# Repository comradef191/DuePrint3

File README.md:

# DuePrint3
Duet 3 to Stratasys PDB Interface Board. Used to convert a Stratasys Prodigy series printer (Dimension, uPrint, Fortus 250) to use a modern control board & firmware. This conversion is fully reversable (assuming the printer functions to begin with). Many thanks to AJ Quick and Archeantus (Jeremy) for their past efforts in detailing the electronics of the Dimension/uPrint machines, as well as sharing details on their Duet 2 WiFi conversions.
* https://wiki.cnc.xyz/Stratasys_uPrint_Retrofit
* https://forum.duet3d.com/topic/12647/another-stratasys-uprint-retrofit

[Additional details for this project on the Duet3D forums.](https://forum.duet3d.com/topic/37434/dueprint-with-a-duet-3-6hc-stratasys-dimension-conversion)

At present, the implementation focuses on the Dimension 1200es printers (the implementations linked above focus on the uPrint series, which is quite similar. The electronics are laid out a touch differently, meaning the layout of the new hardware must change, as well where the stepper motor wiring taps in to the existing harness). The Duet 3 Mainboard 6HC, as well as the Sammy-C21 module (natively running RepRapFirmware) interface with 19 inputs, and 9 outputs.
### Inputs
|Input|Description|GCode|Note|
|---|---|---|---|
|6HC IO_7 io7.in|PRINT HEAD TEMP ALARM|`M950 J9 C"!io7.in" ; Print Head Temp Alarm`|Feature not yet implemented|
|6HC IO_2 io2.in|PRINT BED TOUCH PR LIM SW|`M558 P5 H5 F1200:200 T18000 A3 C"!io2.in" ; Z probe`|Used in bed probing|
|6HC IO_6 io6.in|Z-AXIS EOT|`M574 Z2 S1 P"!io6.in"  ; assign Z EOT to x endstop on high side`|Used as part of homing (find max Z)|
|6HC IO_8 io8.in|CHAMBER TEMP ALARM|`M950 J10 C"!io8.in" ; Chamber Temp Alarm`|Feature not yet implemented|
|6HC IO_4 io4.in|Y-AXIS EOT|`M950 J6 C"!io4.in" ; Y-axis EOT`|Used in macro to measure max Y|
|6HC IO_3 io3.in|X-AXIS EOT|`M950 J5 C"!io3.in" ; X-axis EOT`|Used in macro to measure max X|
|6HC IO_0 io0.in|X-AXIS HOME SW|`M574 X1 S1 P"!io0.in" ; X home limit (low side)`|Used in homing|
|6HC IO_1 io1.in|Y-AXIS HOME SW|`M574 Y1 S1 P"!io1.in" ; Y home limit (low side)`|Used in homing|
|6HC IO_5 io5.in|Z-AXIS HOME SW|`M950 J7 C"!io5.in" ; Z-axis Home`|I/O works, Feature not yet implemented|
|SAMMY-C21 PB08|Filament Detection 2|Not Implemented|Feature not yet implemented|
|SAMMY-C21 PA04|Gecko Error|`M950 J0 C"124.pa04" ; Gecko Error In`|Was used to detect an error on Geckodrive G320x. No longer used|
|SAMMY-C21 PA05|HEAD THERMOSTAT STATUS|`M950 J1 C"124.pa05" ;Head Thermostat Status`|Feature not yet implemented|
|SAMMY-C21 PA06|DOOR SWITCH|`M950 J2 C"124.pa06" ; Door`|I/O works, Feature not yet implemented|
|SAMMY-C21 PA07|SUPPORT TOGGLE SW|`M950 J3 C"124.pa07" ; Support Toggle`|Sense Support toolchange|
|SAMMY-C21 PA12|Filament Detection 1|Not Implemented|Feature not yet implemented|
|SAMMY-C21 PA19|MODEL TOGGLE SW|`M950 J4 C"124.pa19" ; Model Toggle`|Sense Model toolchange|
|6HC TEMP_0 VSSA & temp0|CHAMBER THERM|`M308 S0 A"Chamber Test" P"temp0" Y"linear-analog" F0 B-42 C113`||
|6HC TEMP_1 VSSA & temp1|MODEL THERM|`M308 S1 A"Model Test" P"temp1" Y"linear-analog" F0 B12.5 C328`||
|6HC TEMP_2 VSSA & temp2|SUPPORT THERM|`M308 S2 A"Support Test" P"temp2" Y"linear-analog" F0 B12.5 C328`||

### Outputs
|Output|Description|GCode|Note|
|---|---|---|---|
|6HC OUT_8 V_OUTLC8 & out8|EXTRUDER MODEL HEATER ENA|`M950 H1 C"!out8" T1 ; Model, sensor 1`|
|6HC OUT_9 V_OUTLC9 & out9|SUPPORT HEATER ENA|`M950 H2 C"!out9" T2 ; Support, sensor 2`|
|6HC IO_2 io2.out|LED LIGHTS ENA|`M950 P4 C""io2.out"" ; LED Lights - M42 P4 S1 ; lights on`|
|6HC IO_6 io6.out|DOOR SOLENOID ENA|`M950 P3 C""io6.out"" ; Door Solenoid - M42 P3 S0 ; unlocked`|
|6HC OUT_7 V_OUTLC7 & out7|CHAMBER HEATER ENA|`M950 H0 C"!out7" T0 ; Chamber, sensor 0`||
|6HC OUT_6 V_OUTLC6 & out6|PRINT BED TOUCH PR ENA|`M950 P2 C""!out6"" ; Touch Power Enable` - `M42 P2 S0`|Unsure on purpose? Doesn't seem to function at all/as expected|
|6HC IO_0 io0.out|GECKO RESET|`M950 P5 C""io0.out"" ; Gecko Reset` - `M42 P5 S0`|Was used to reset an error on Geckodrive G320x. No longer used|
|6HC OUT_5 V_OUTLC5 & out5|MOTOR ENA|`M950 P1 C""!out5"" ; Extruder Motor` - `M42 P1 S0 ; motor off`|
|6HC OUT_4 V_OUTLC4 & out4|BLOWER ENA|`M950 P0 C""!out4"" ; Head Blower Fan` - `M42 P0 S0 ; enable blower`|

The 6HC directly drives the X, Y, and Z stepper motors (vs. controlling them through the Stratasys PDB). The 6HC, unlike the Duet2 (and Duex boards) does not natively have STEP/DIR pins used to emit step and direction pulses. Instead, a Sammy-C21 ([running RepRapFirmware](https://docs.duet3d.com/Duet3D_hardware/Duet_3_family/Using_the_Sammy-C21_development_board_with_Duet_3)) is used to emit step and direction pulses to a STM32 Nucelo-64, which in turn is running [SimpleDCMotor](https://github.com/simplefoc/Arduino-FOC-dcmotor) to control the extruder's closed loop DC motor. Note that this design was initially setup to use a Geckodrive G320x, however early into commissioning, I burnt up a few series resistors and a 74AC14 on the PDB. The Nucleo-64 with SimpleDCMotor is a much better solution, with a significantly lower cost.

## Materials
[A detailed BOM can be found here](https://github.com/jcwebber93/DuePrint3/blob/main/DuePrint3%20BOM.xlsx), with the approximate cost being ~$500 (60% of this is Duet3D 6HC and Sammy-C21).

## Interface Board Design
[The KidCad project for the DuePrint3 board can be found here](https://github.com/jcwebber93/DuePrint3/tree/main/DuePrint3%20KiCad%20Project)

## Wiring
[A detailed wire list can be found here.](https://github.com/jcwebber93/DuePrint3/blob/main/DuePrint3%20Wire%20List.xlsx) Connectors & crimps for the Duet 3 6HC are supplied with the board, but are JST VH (stepper motors) and Molex KK / Wurth WR-WTB (Wurth connectors/contacts are supplied with Duet Boards). Interface board uses Molex Micro-3.0 series connectors & crimps, whereas the connectors for the PBD ribbon cables are Samtec EHT headers.

> [!WARNING]
> Do not connect connectors `P13`, `P20`, and `P26` (Model heater, support heater, chamber heater) to the 6HC until after the model, support, and chamber thermocouple functionality has been validated

## Sammy-C21 Prep
If using a Sammy-C21 purchased with the preloaded Duet3D bootloader, no special programming is needed. J100 needs to be unbridged, as 5V is supplied to pins 15 and 32 (V33, for 5V logic, and VCC).

## Interface Board Prep
If the Interface Board (w/Sammy-C21) is the only CAN-FD device, aside from the Duet 3 6HC, place a 2-socket jumper here to enable the CAN-FD termination resistor.

J4 connects to the 6HC. J5 (marking suspiciously missing on silkscreen) can be used with additional expansion boards (such as a Duet 3 SZP on the print head, could be used as an accelerometer or for bed scanning), provided the CAN-FD bus is terminated on the additional board.

## RepRapFirmware Prep
At present, the 6HC and Sammy-C21 are running 3.6.0-rc.1 (April 2025). [Configuration files are located here](https://github.com/jcwebber93/DuePrint3/tree/main/Duet%203%20Configuration/System%20Directory), and [Macros are located here.](https://github.com/jcwebber93/DuePrint3/tree/main/Duet%203%20Configuration/Macros%20Directory)

> [!WARNING]
> Do not connect connectors `P13`, `P20`, and `P26` (Model heater, support heater, chamber heater) to the 6HC until after the model, support, and chamber thermocouple functionality has been validated (a spare K-type thermocouple can be used to validate the linear-analog values in the `M308` commands - ice water and boiling water (for the chamber), boiling water for the extruders)

## SimpleDCMotor / Nucleo-64
[Sketch located here](https://github.com/jcwebber93/DuePrint3/tree/main). Prep your build enviornment [per the SimpleFOC documentation.](https://docs.simplefoc.com/) I used Ardiono IDE, and [added boards via](https://github.com/stm32duino/Arduino_Core_STM32/wiki/Getting-Started). I bench programmed the Nucleo-64, then prepped it for install in the Stratasys by janging jumper JP5 to set power via E5V instead of U5V (USB).

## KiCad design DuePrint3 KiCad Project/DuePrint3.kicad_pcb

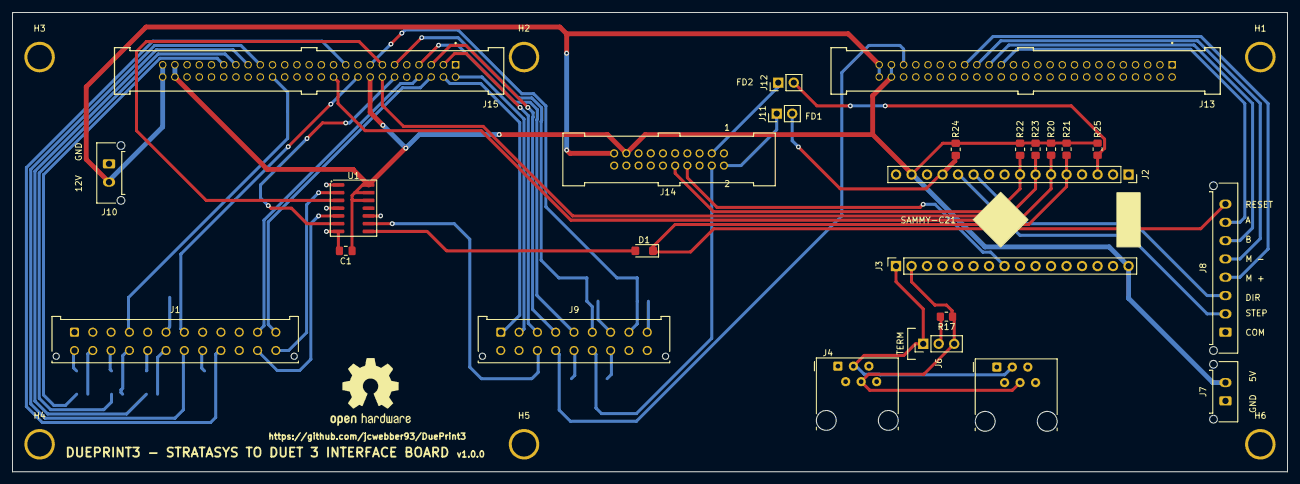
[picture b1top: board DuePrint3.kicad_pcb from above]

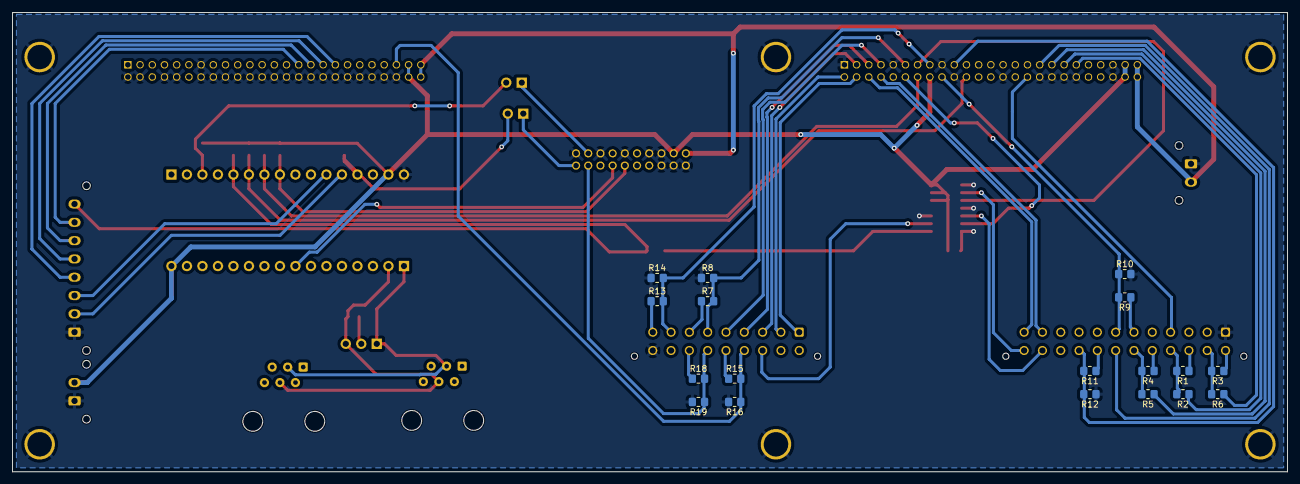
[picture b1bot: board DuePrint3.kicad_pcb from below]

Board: 2 copper layers, 208.9 x 75.2 mm, 49 parts (18 on the bottom side), 56 nets.

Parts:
C1: 0.1 µF; C_0805_2012Metric_Pad1.18x1.45mm_HandSolder
D1: 100v 1A; D_SMF
H1, H2, H3, H4, H5, H6: MountingHole_Pad; MountingHole_4.00mm_Pad
J1: MF3.0-2x12-430452412; Molex_Micro-Fit_3.0_43045-2412_2x12_P3.00mm_Vertical
J2, J3: 2.54Header-1x16-F; PinSocket_1x16_P2.54mm_Vertical
J4, J5: 6P2C; RJ12_Amphenol_54601-x06_Horizontal
J6: 2.54Header-1x3-M; PinHeader_1x03_P2.54mm_Vertical
J7, J10: MF3.0-1x2-436500215; Molex_Micro-Fit_3.0_43650-0215_1x02_P3.00mm_Vertical
J8: MF3.0-1x8-436500815; Molex_Micro-Fit_3.0_43650-0815_1x08_P3.00mm_Vertical
J9: MF3.0-2x9-430451812; Molex_Micro-Fit_3.0_43045-1812_2x09_P3.00mm_Vertical
J11, J12: 2.54Header-1x2-M; PinHeader_1x02_P2.54mm_Vertical
J13, J15: EHT-125-01-S-D; SAMTEC_EHT-125-01-S-D
J14: EHT-110-01-S-D; EHT-110-01-XX-D
R1, R3, R4: 2K; R_0805_2012Metric_Pad1.20x1.40mm_HandSolder
R2, R5, R6: 1K; R_0805_2012Metric_Pad1.20x1.40mm_HandSolder
R7, R9, R11, R13, R15, R18: 31.6K; R_0805_2012Metric_Pad1.20x1.40mm_HandSolder
R8, R10, R12, R14, R16, R19: 3740; R_0805_2012Metric_Pad1.20x1.40mm_HandSolder
R17: 120; R_0805_2012Metric_Pad1.20x1.40mm_HandSolder
R20, R21, R22, R23, R24, R25: 10k; R_0805_2012Metric_Pad1.20x1.40mm_HandSolder
U1: SN74AHCT125DR; SOIC-14_3.9x8.7mm_P1.27mm

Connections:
+5V: C1.1, J2.15, J3.16, J7.2, J13.47, J13.48, J14.17, J15.16, J15.47, J15.48, R20.2, R21.2, R22.1, R23.1, R24.1, R25.1, U1.12 (4A), U1.13 (4~OE), U1.14 (VCC)
+12V: J10.2, J13.49, J13.50, J14.19, J15.49, J15.50
/T0: J1.13, J1.14, R3.1, R3.2, R6.1
/T1: J1.18, R4.2, R5.1
/T1 VSSA: J1.17, R4.1
/T2: J1.16, R1.2, R2.1
/T2 VSSA: J1.15, R1.1
ARMATURE NEGATIVE: J8.5, J13.33
ARMATURE POSITIVE: J8.4, J13.35
CAN0H: J3.1, J4.3, J5.3, J6.1
CAN0L: J3.2, J4.4, J5.4, J6.3, R17.1
CHAMBER HEATER ENABLE: J9.6, J15.11, R7.2, R8.1
CHAMBER TEMP ALARM: J1.19, J15.33
CHAMBER TEMP THERM: J15.39, R6.2
DIR: J2.11, J8.3
DOOR SOLENOID ENABLE: J15.13, U1.3 (1Y)
DOOR SWITCH: J2.7, J15.14, R23.2
EMHE PWM: J1.7, J15.18, R9.2, R10.1
ENCODER CH A: J8.7, J13.29
ENCODER CH B: J8.6, J13.31
ESHE PWM: J1.21, J15.19, R11.2, R12.1
FD1: J11.1, J14.2
FD2: J12.1, J14.3
GECKO ERROR: D1.1 (K), J2.5, J8.8, R21.1
GND: C1.2, H1.1, H2.1, H3.1, H4.1, H5.1, H6.1, J1.1, J2.16, J7.1, J8.1, J9.18, J10.1, J13.2, J13.4, J13.8, J13.10, J13.13, J13.14, J13.16, J13.18, J13.20, J13.22, J13.24, J13.26, J13.28, J13.30, J13.32, J13.34, J13.36, J13.38, J13.40, J13.42, J13.44, J13.46, J14.1, J14.5, J14.9, J14.13, J14.15, J14.16, J14.18, J14.20, J15.1, J15.9, J15.17, J15.20, J15.24, J15.26, J15.28, J15.34, J15.36, J15.38, J15.40, J15.45, J15.46, R8.2, R10.2, R12.2, R14.2, R16.2, R19.2, U1.1 (1~OE), U1.4 (2~OE), U1.7 (GND), U1.10 (3~OE)
HEAD THERMOSTAT STATUS: J2.6, J15.22, R20.1
LED Lights Enable: J15.12, U1.6 (2Y)
LS DOOR SOLENOID ENABLE: J1.24, U1.2 (1A)
LS GECKO RESET: J9.12, U1.9 (3A)
LS LED Lights Enable: J1.23, U1.5 (2A)
MOTOR ENABLE: J9.13, J13.45, R15.2, R16.1
unnamed: D1.2 (A), U1.8 (3Y)
unnamed: J6.2, R17.2
unnamed: J2.13, J11.2, R24.2
unnamed: J2.3, J12.2, R25.2
PBTPE PWM: J9.8, J15.15, R13.2, R14.1
PHBE PWM: J9.15, J14.4, R18.2, R19.1
PRINT BED TOUCH PR LIM SW: J1.11, J15.8
PRINT HEAD MODEL THEM: J15.35, R5.2
PRINT HEAD SUPP THEM: J15.37, R2.2
PRINT HEAD TEMP ALARM: J1.4, J15.32
Print Head Model Toggle SW: J3.8, J14.8
Print Head Support Toggle SW: J2.8, J14.10, R22.2
STEP: J2.12, J8.2
VD CHAMBER HEATER ENABLE: J9.7, R7.1
VD EXTRUDER MODEL HEATER ENABLE: J1.6, R9.1
VD EXTRUDER SUPPORT HEATER ENABLE: J1.20, R11.1
VD MOTOR ENABLE: J9.14, R15.1
VD PRINT BED TOUCH PR PWR EN: J9.9, R13.1
VD PRINT HEAD BLOWER ENABLE: J9.16, R18.1
X-AXIS HOME LIM SW: J9.3, J15.3
X-Axis End of Travel Lim SW: J9.2, J15.2
Y-AXIS HOME LIM SW: J9.4, J15.5
Y-Axis End of Travel Lim SW: J9.1, J15.4
Z-AXIS HOME LIM SW: J9.5, J15.7
Z-Axis End of Travel Lim SW: J1.12, J15.6

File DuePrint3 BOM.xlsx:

|  |  |  |  | 471.0900000000002
Item | Part Number | Description | Quantity | REF | Price | EXT Price | Note | Link
1 |  | Duet 3 Mainboard 6HC | 1 |  | 269.99 | 269.99 |  | https://www.filastruder.com/collections/duet3d/products/duet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
2 | C45_SC21-D3D | SAMMY-C21 Module | 1 |  | 34.99 | 34.99 | Likely need to source 16pin headers | https://www.filastruder.com/products/sammy-c21-v1-0-duet3d-module
3 | NUCLEO-L476RG | STM32 Nucleo-64, L476RG | 1 |  | 23.99 | 23.99 | Need USB Mini B cable for programming | https://www.amazon.com/dp/B01IO3N646
4 |  | DuePrint3 v1.0.0 PCB | 1 |  | 40.6 | 40.6
5 | LRS-75-48 | Power Suppy, AC/DC, 48V 75W | 1 |  | 15.6 | 15.6 | AC is spliced in from the printer's power inlet, meaning right now the Duet's p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 | https://www.digikey.com/en/products/detail/mean-well-usa-inc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
6 | 430452412 | Conn, Header, 24 pos, Micro-Fit 3.0 | 1 | J1 | 3.51 | 3.51 |  | https://www.digikey.com/en/products/detail/molex/0430452412/531416
7 | 430451812 | Conn, Header, 18 pos, Micro-Fit 3.0 | 1 | J9 | 2.48 | 2.48 |  | https://www.digikey.com/en/products/detail/molex/0430451812/531413
8 | EHT-120-01-S-D | Conn, Header, 40 pos, EHT | 2 | J13,J15 | 13.46 | 26.92 |  | https://www.digikey.com/en/products/detail/samtec-inc/EHT-12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
9 | EHT-110-01-S-D | Conn, Header, 20 pos, EHT | 1 | J14 | 6.54 | 6.54 |  | https://www.digikey.com/en/products/detail/samtec-inc/EHT-11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
10 | PPPC161LFBN-RC | Conn, Header, 16 pos | 2 | J2,J3 | 0.93 | 1.86 |  | https://www.digikey.com/en/products/detail/sullins-connector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
11 | 54601-906002WPLF | Conn, 6p4c R/A | 2 | J4,J5 | 0.2 | 0.4 |  | https://www.digikey.com/en/products/detail/amphenol-cs-fci/5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
12 | 436500215 | Conn, Header, 2 pos, MicroFit- 3.0 | 2 | J7,J10 | 0.89 | 1.78 |  | https://www.digikey.com/en/products/detail/molex/0436500215/283461
13 | M20-9990245 | Conn, Header, 2 pos | 2 | J11,J12 | 0.12 | 0.24 | Can buy larger and cut down | https://www.digikey.com/en/products/detail/harwin-inc/M20-99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
14 | M20-9990345 | Conn, Header, 3 pos | 1 | J6 | 0.15 | 0.15 | Can buy larger and cut down | https://www.digikey.com/en/products/detail/harwin-inc/M20-99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
15 | 436500815 | Conn, Header, 8 pos, Micro-Fit 3.0 | 1 | J8 | 1 | 1 |  | https://www.digikey.com/en/products/detail/molex/0436500815/531388
16 | CL21B104KCFSFNE | 0.1 uF Cap, 0805 | 1 | C1 | 0.1 | 0.1 |  | https://www.digikey.com/en/products/detail/samsung-electro-m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
17 | CRCW080531K6FKEA | 31.6K Res, 0805 | 6 | R7,R9,R11,R13,R15,R18 | 0.1 | 0.60000000000000009 |  | https://www.digikey.com/en/products/detail/vishay-dale/CRCW0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
18 | CRCW08053K74FKEA | 3740 Res, 0805 | 6 | R8,R10,R12,R14,R16,R19 | 0.1 | 0.60000000000000009 |  | https://www.digikey.com/en/products/detail/vishay-dale/crcw0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
19 | CRCW080510K0FKEA | 10K Res, 0805 | 6 | R20,R21,R22,R23,R24,R25 | 0.1 | 0.60000000000000009 |  | https://www.digikey.com/en/products/detail/vishay-dale/crcw0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
20 | CRCW08052K00FKEA | 2K Res, 0805 | 3 | R1,R3,R4 | 0.1 | 0.30000000000000004 |  | https://www.digikey.com/en/products/detail/vishay-dale/CRCW0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
21 | CRCW08051K00FKEA | 1K Res, 0805 | 3 | R2,R5,R6 | 0.1 | 0.30000000000000004 |  | https://www.digikey.com/en/products/detail/vishay-dale/CRCW0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
22 | CRCW08051K00FKEA | 120 Res, 0805 | 1 | R17 | 0.1 | 0.1 |  | https://www.digikey.com/en/products/detail/vishay-dale/CRCW0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
23 | SS1FH10-M3/H | Schottky Diode, 100V 1A, DO-219AB | 1 | D1 | 0.32 | 0.32 |  | https://www.digikey.com/en/products/detail/vishay-general-se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
24 | SN74AHCT125DR | SN74AHCT125DR, 14-SOIC | 1 | U1 | 0.23 | 0.23 |  | https://www.digikey.com/en/products/detail/texas-instruments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
25 | 39012086 | Conn, Plug, 8 pos, Mini-Fit Jr | 1 | P2 | 0.66 | 0.66 |  | https://www.digikey.com/en/products/detail/molex/0039012086/930285
26 | 39012205 | Conn, Rcpt, 20 pos, Mini-Fit Jr | 1 | P3 | 1.48 | 1.48 |  | https://www.digikey.com/en/products/detail/molex/0039012205/930279
27 | 39012206 | Conn, Plug, 20 pos, Mini-Fit Jr | 1 | P1 | 1.2 | 1.2 |  | https://www.digikey.com/en/products/detail/molex/0039012206/4693014
28 | 39000041 | Pin, 18-24 AWG, Mini-Fit Jr | 10 |  | 0.15 | 1.5 | Don't use these, as they're designed for very large jackets. Recommend 39000049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 | https://www.digikey.com/en/products/detail/molex/0039000041/61445
29 | 39000039 | Socket, 18-24 AWG, Mini-Fit Jr | 6 |  | 0.16 | 0.96 | Don't use these, as they're designed for very large jackets. Recommend 39000047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 | https://www.digikey.com/en/products/detail/molex/0039000039/61448
30 | 430300007 | Socket, 20-24 AWG, Micro-Fit 3.0 | 43 |  | 0.18 | 7.7399999999999993 |  | https://www.digikey.com/en/products/detail/molex/0430300007/252479
31 | 430252400 | Conn, Rcpt, 24 pos, Micro-Fit 3.0 | 1 | P8 | 1.34 | 1.34 |  | https://www.digikey.com/en/products/detail/molex/0430252400/531410
32 | 430251800 | Conn, Rcpt, 18 pos, Micro-Fit 3.0 | 1 | P9 | 1.07 | 1.07 |  | https://www.digikey.com/en/products/detail/molex/0430251800/531407
33 | 436450800 | Conn, Rcpt, 8 pos, Micro-Fit 3.0 | 1 | P10 | 0.35 | 0.35 |  | https://www.digikey.com/en/products/detail/molex/0436450800/531322
34 | VHR-4N | Conn, Rcpt, 4 pos, JST VH | 3 | P4,P5,P6 | 0.12 | 0.36 | Included in 6HC purchase | https://www.digikey.com/en/products/detail/jst-sales-america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
35 | SVH-21T-P1.1 | Socket, 18-22 AWG, JST VH | 12 |  | 0.12 | 1.44 | Included in 6HC purchase | https://www.mouser.com/ProductDetail/JST-Commercial/SVH-21T-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
36 | 61900511621 | Conn, Rcpt, 5 pos, WR-WTB | 9 | P12,P14,P15,P19,P21,P22,P23,P24,P25 | 0.17 | 1.53 | Included in 6HC purchase | https://www.digikey.com/en/products/detail/w%C3%BCrth-elektr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
37 | 61900211621 | Conn, Rcpt, 2 pos, WR-WTB | 6 | P13,P16,P17,P18,P20,P26 | 0.13 | 0.78 | Included in 6HC purchase | https://www.digikey.com/en/products/detail/w%C3%BCrth-elektr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
38 | 61900411621 | Conn, Rcpt, 4 pos, WR-WTB | 3 | P27,P28,P29 | 0.17 | 0.51 | Included in 6HC purchase | https://www.digikey.com/en/products/detail/w%C3%BCrth-elektr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
39 | 61900113722DEC | Socket, 22-28 AWG, WR-WTB | 32 |  | 0.15 | 4.8 | Included in 6HC purchase | https://www.digikey.com/en/products/detail/w%C3%BCrth-elektr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
40 | QPC02SXGN-RC | Jumper, Shorting | 2 |  | 0.1 | 0.2 | For CAN-FD termination, or later filament detector connection | https://www.digikey.com/en/products/detail/sullins-connector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
41 |  | CAN-FD Cable, 1m | 1 |  | 4.99 | 4.99 |  | https://www.filastruder.com/collections/duet3d/products/duet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
42 |  | 120pcs 200mm Dupont Jumpers | 1 |  | 6.98 | 6.98 | As required | https://www.amazon.com/dp/B01EV70C78
43 |  | 22 AWG Wire |  |  |  | 0 | As required/desired. Smaller gauges likely would be acceptable for most connect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 | https://www.remingtonindustries.com/hook-up-wire/hook-up-wir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
44 |  | RJ11 connectors |  |  |  | 0 | In case custom length/custom purpose CAN-FD cables are desired

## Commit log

2025-04-05 Initial Release
    KiCad Project, wire list
2025-04-05 Updated Wire List, BOM
2025-04-05 Add Duet 3 configuration files
2025-04-06 File updates
2025-04-07 SimpleDC Sketch
2025-04-26 Reformat Duet3 connectors
2025-04-26 Voltage Dividers
2025-04-26 Level shifter
2025-04-26 PDB Connectors
2025-04-26 The Rest Of The Schematic
2025-04-26 also kicad gitignore pls
2025-04-26 Footprint & Symbol reorg; PCB & Schematic now cleaned-up
